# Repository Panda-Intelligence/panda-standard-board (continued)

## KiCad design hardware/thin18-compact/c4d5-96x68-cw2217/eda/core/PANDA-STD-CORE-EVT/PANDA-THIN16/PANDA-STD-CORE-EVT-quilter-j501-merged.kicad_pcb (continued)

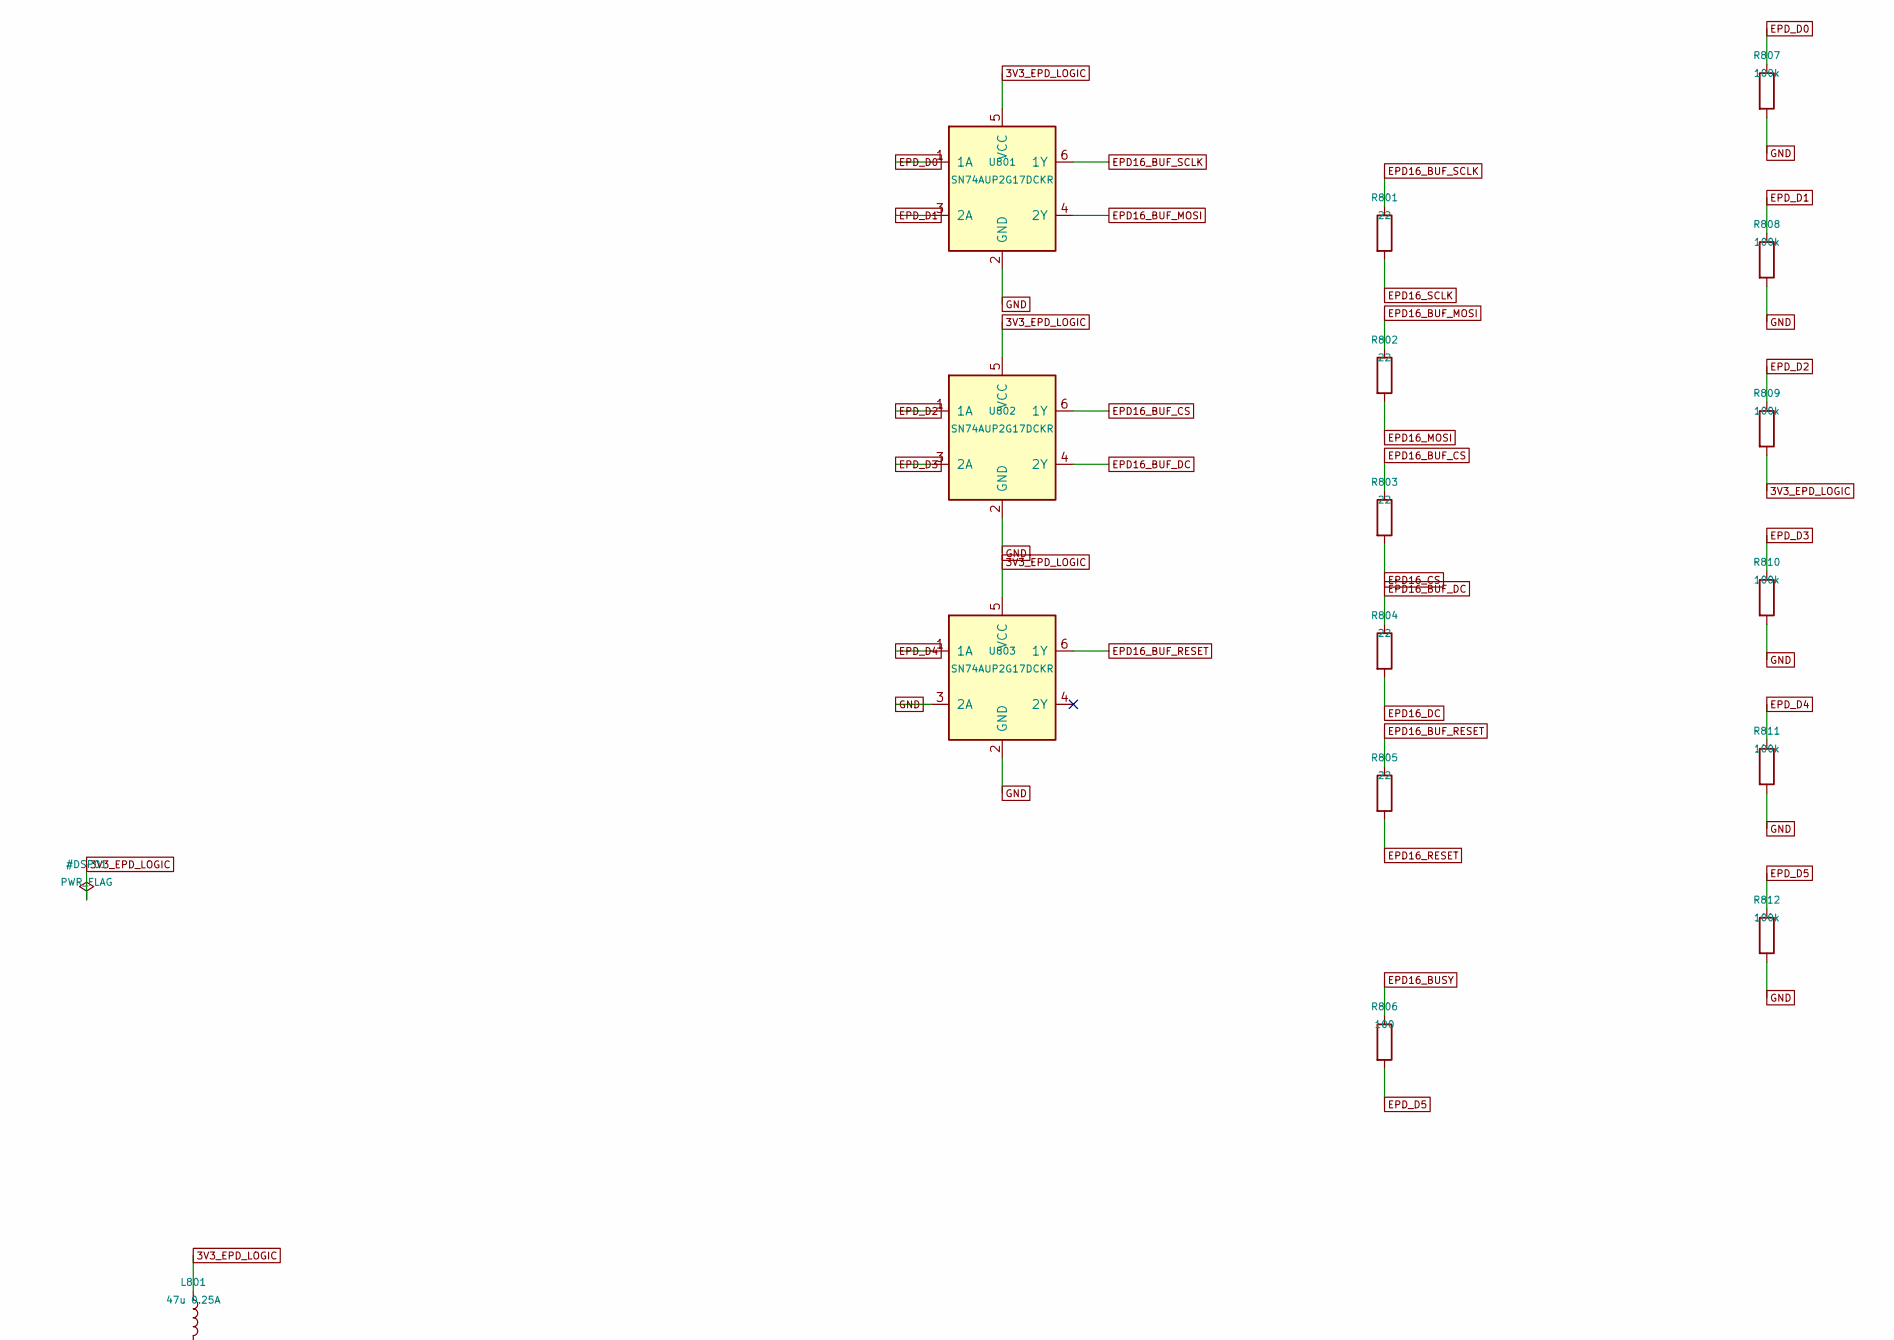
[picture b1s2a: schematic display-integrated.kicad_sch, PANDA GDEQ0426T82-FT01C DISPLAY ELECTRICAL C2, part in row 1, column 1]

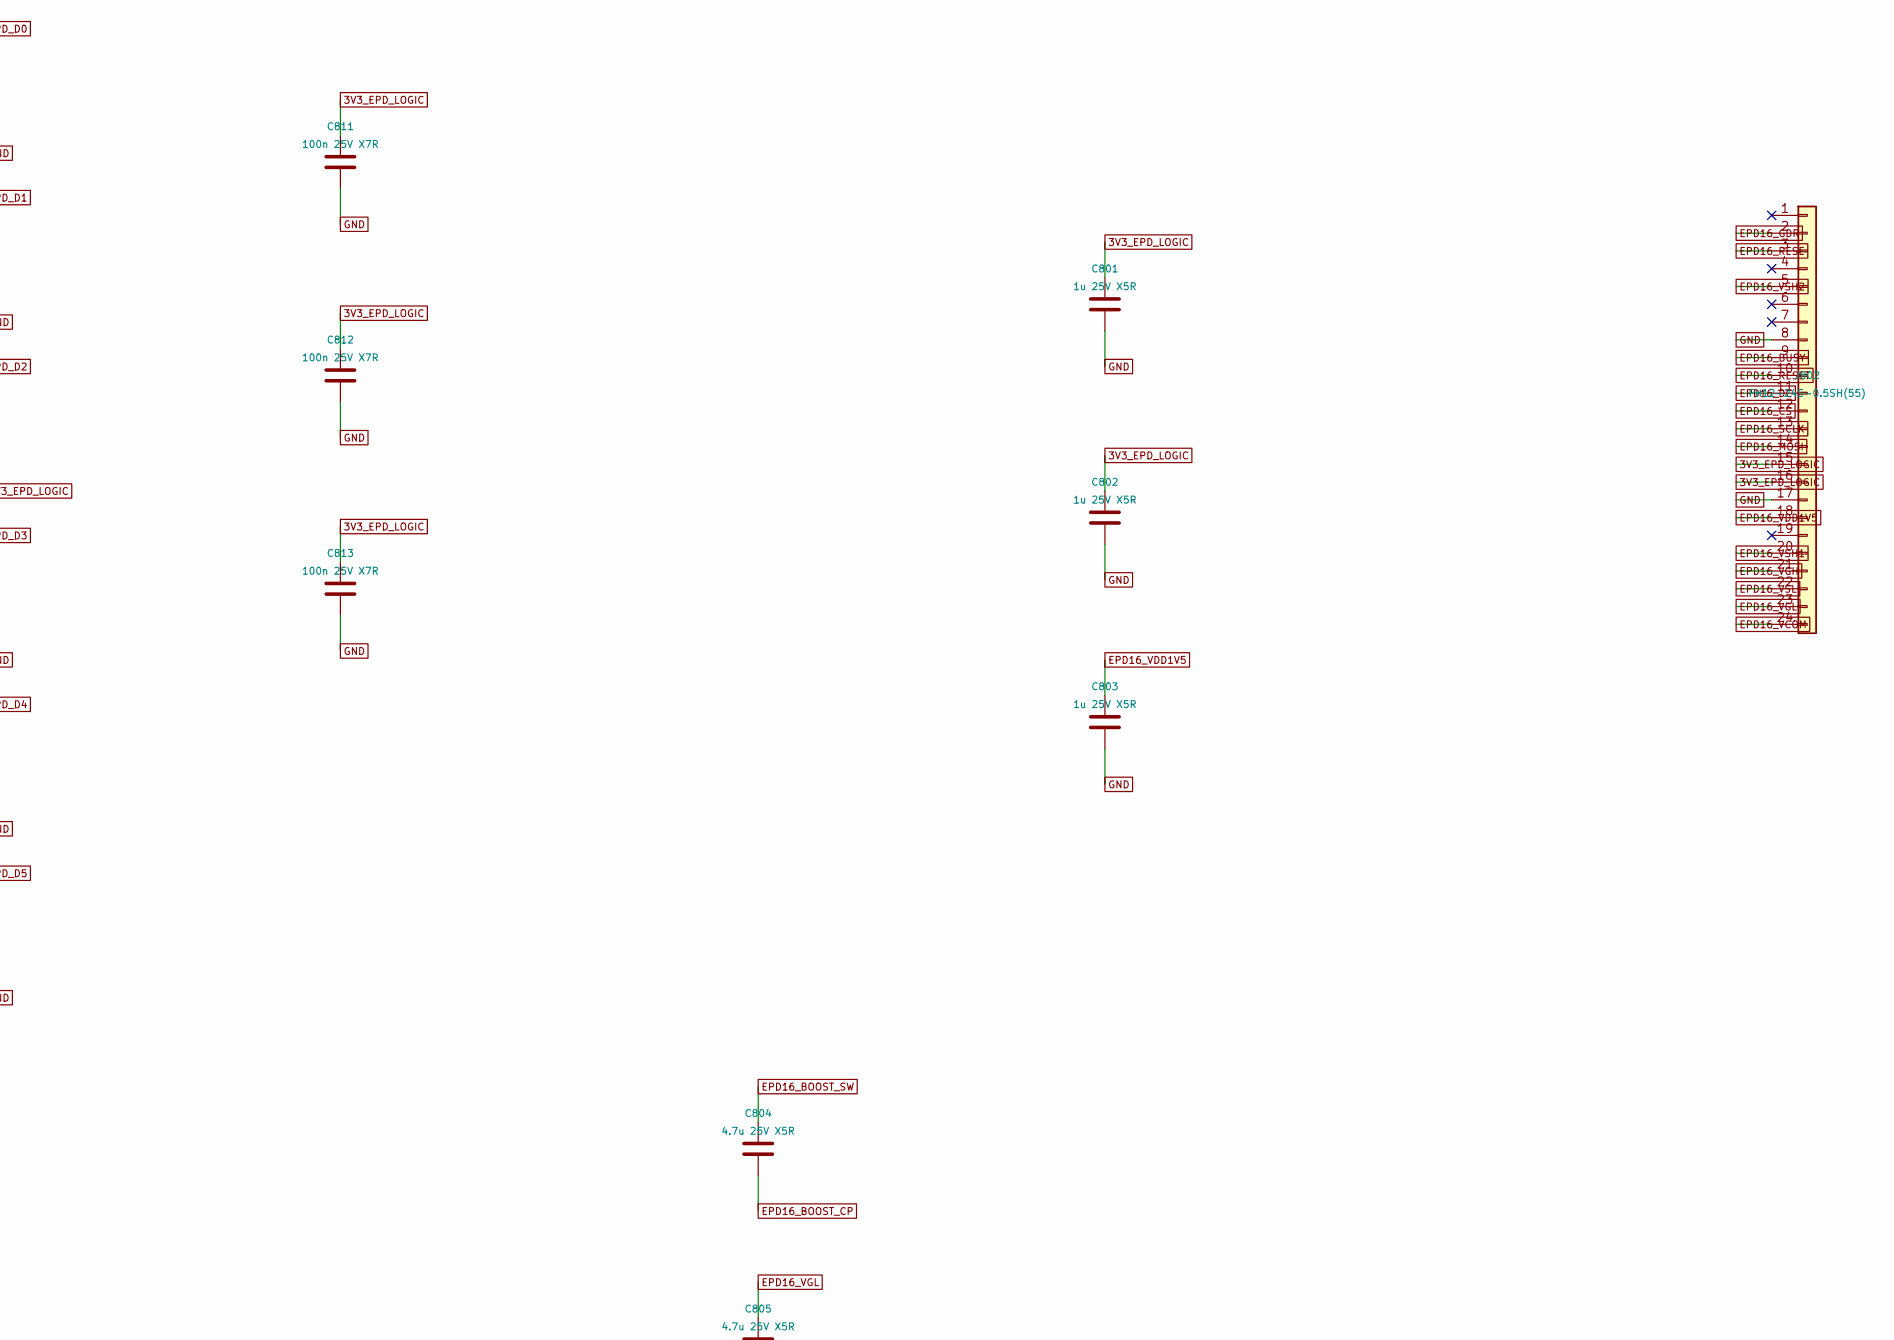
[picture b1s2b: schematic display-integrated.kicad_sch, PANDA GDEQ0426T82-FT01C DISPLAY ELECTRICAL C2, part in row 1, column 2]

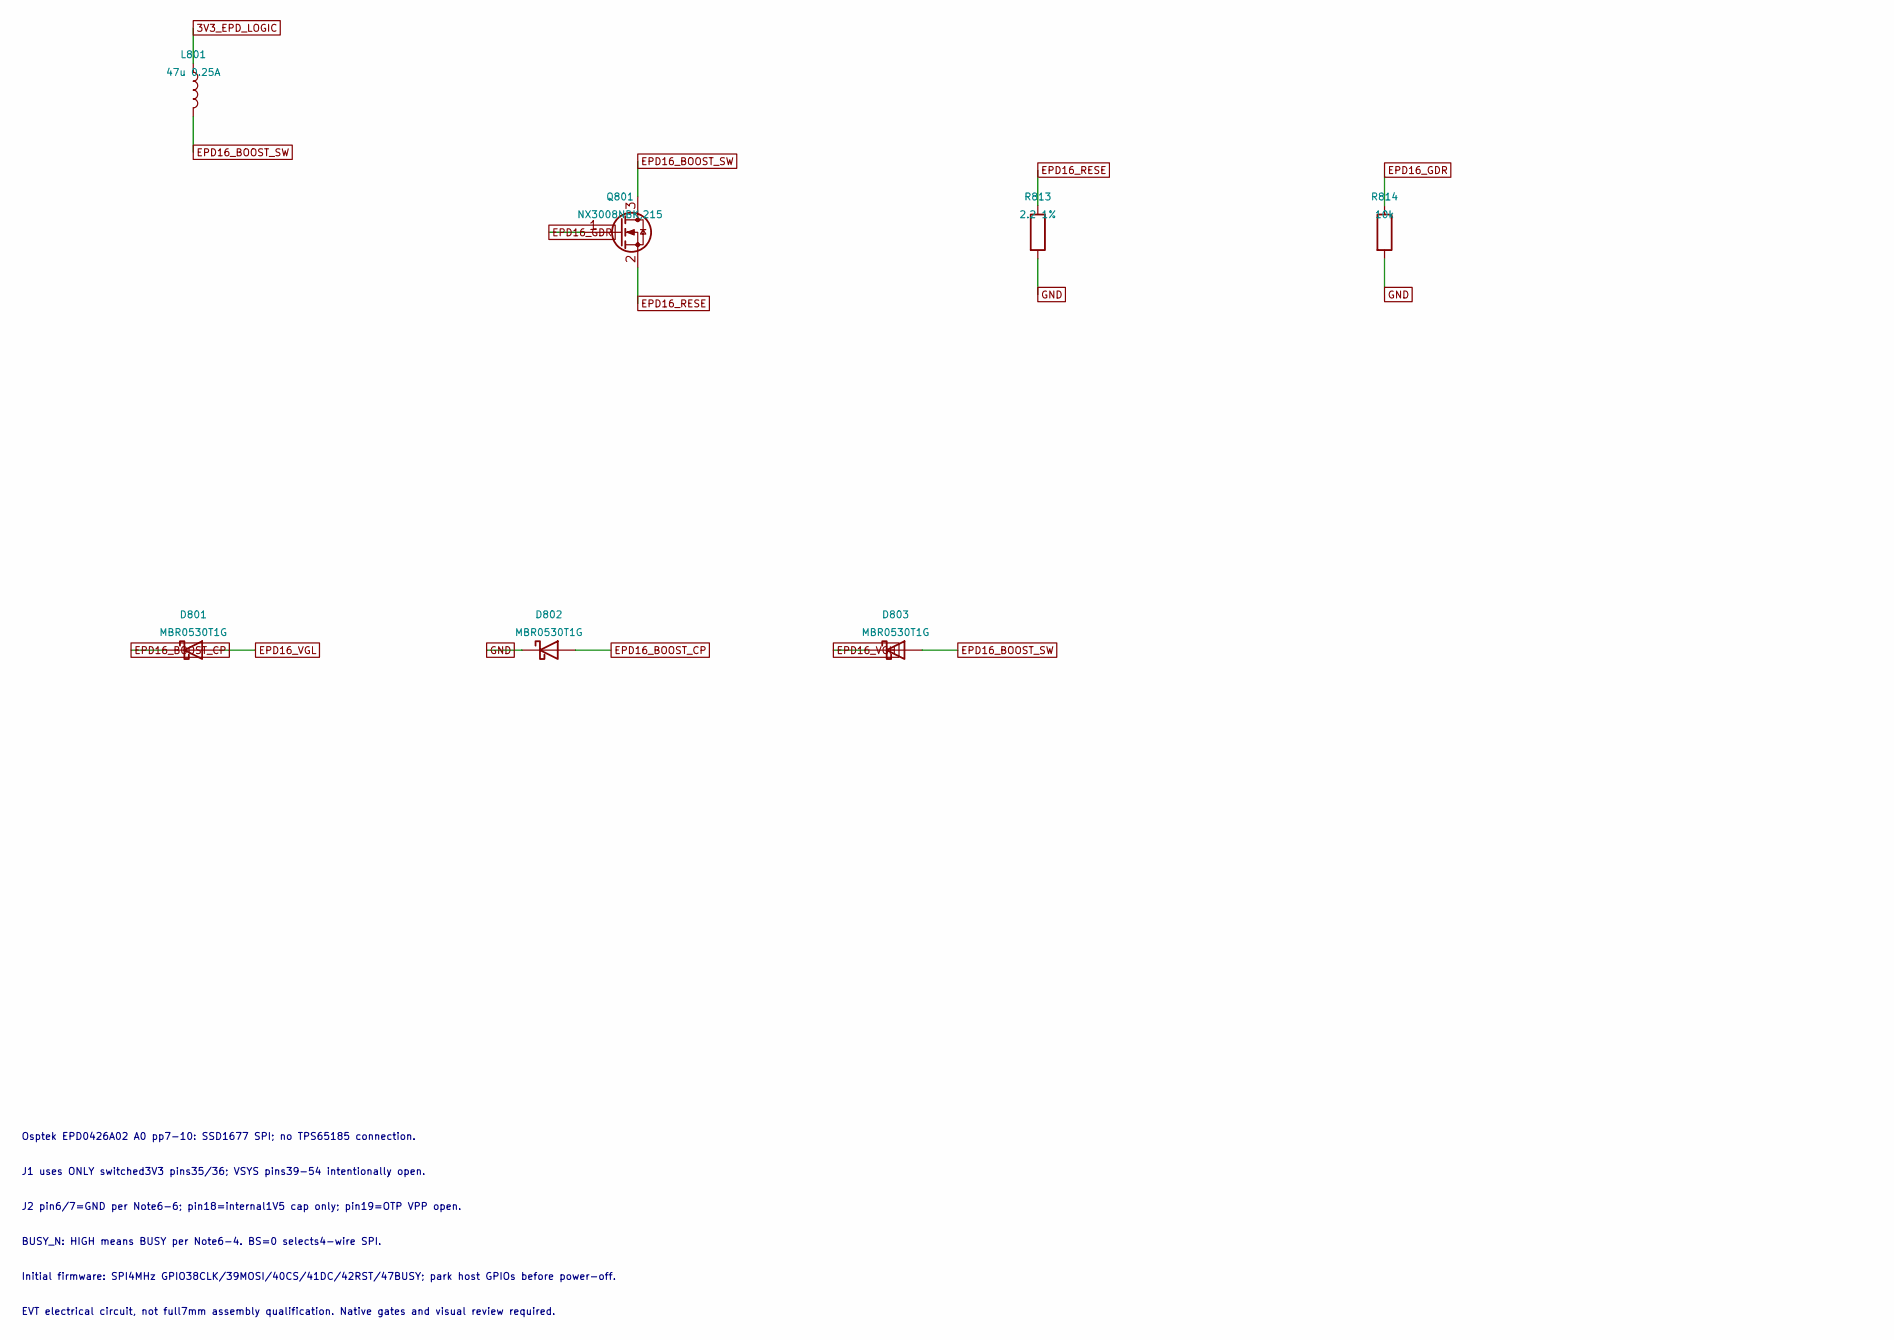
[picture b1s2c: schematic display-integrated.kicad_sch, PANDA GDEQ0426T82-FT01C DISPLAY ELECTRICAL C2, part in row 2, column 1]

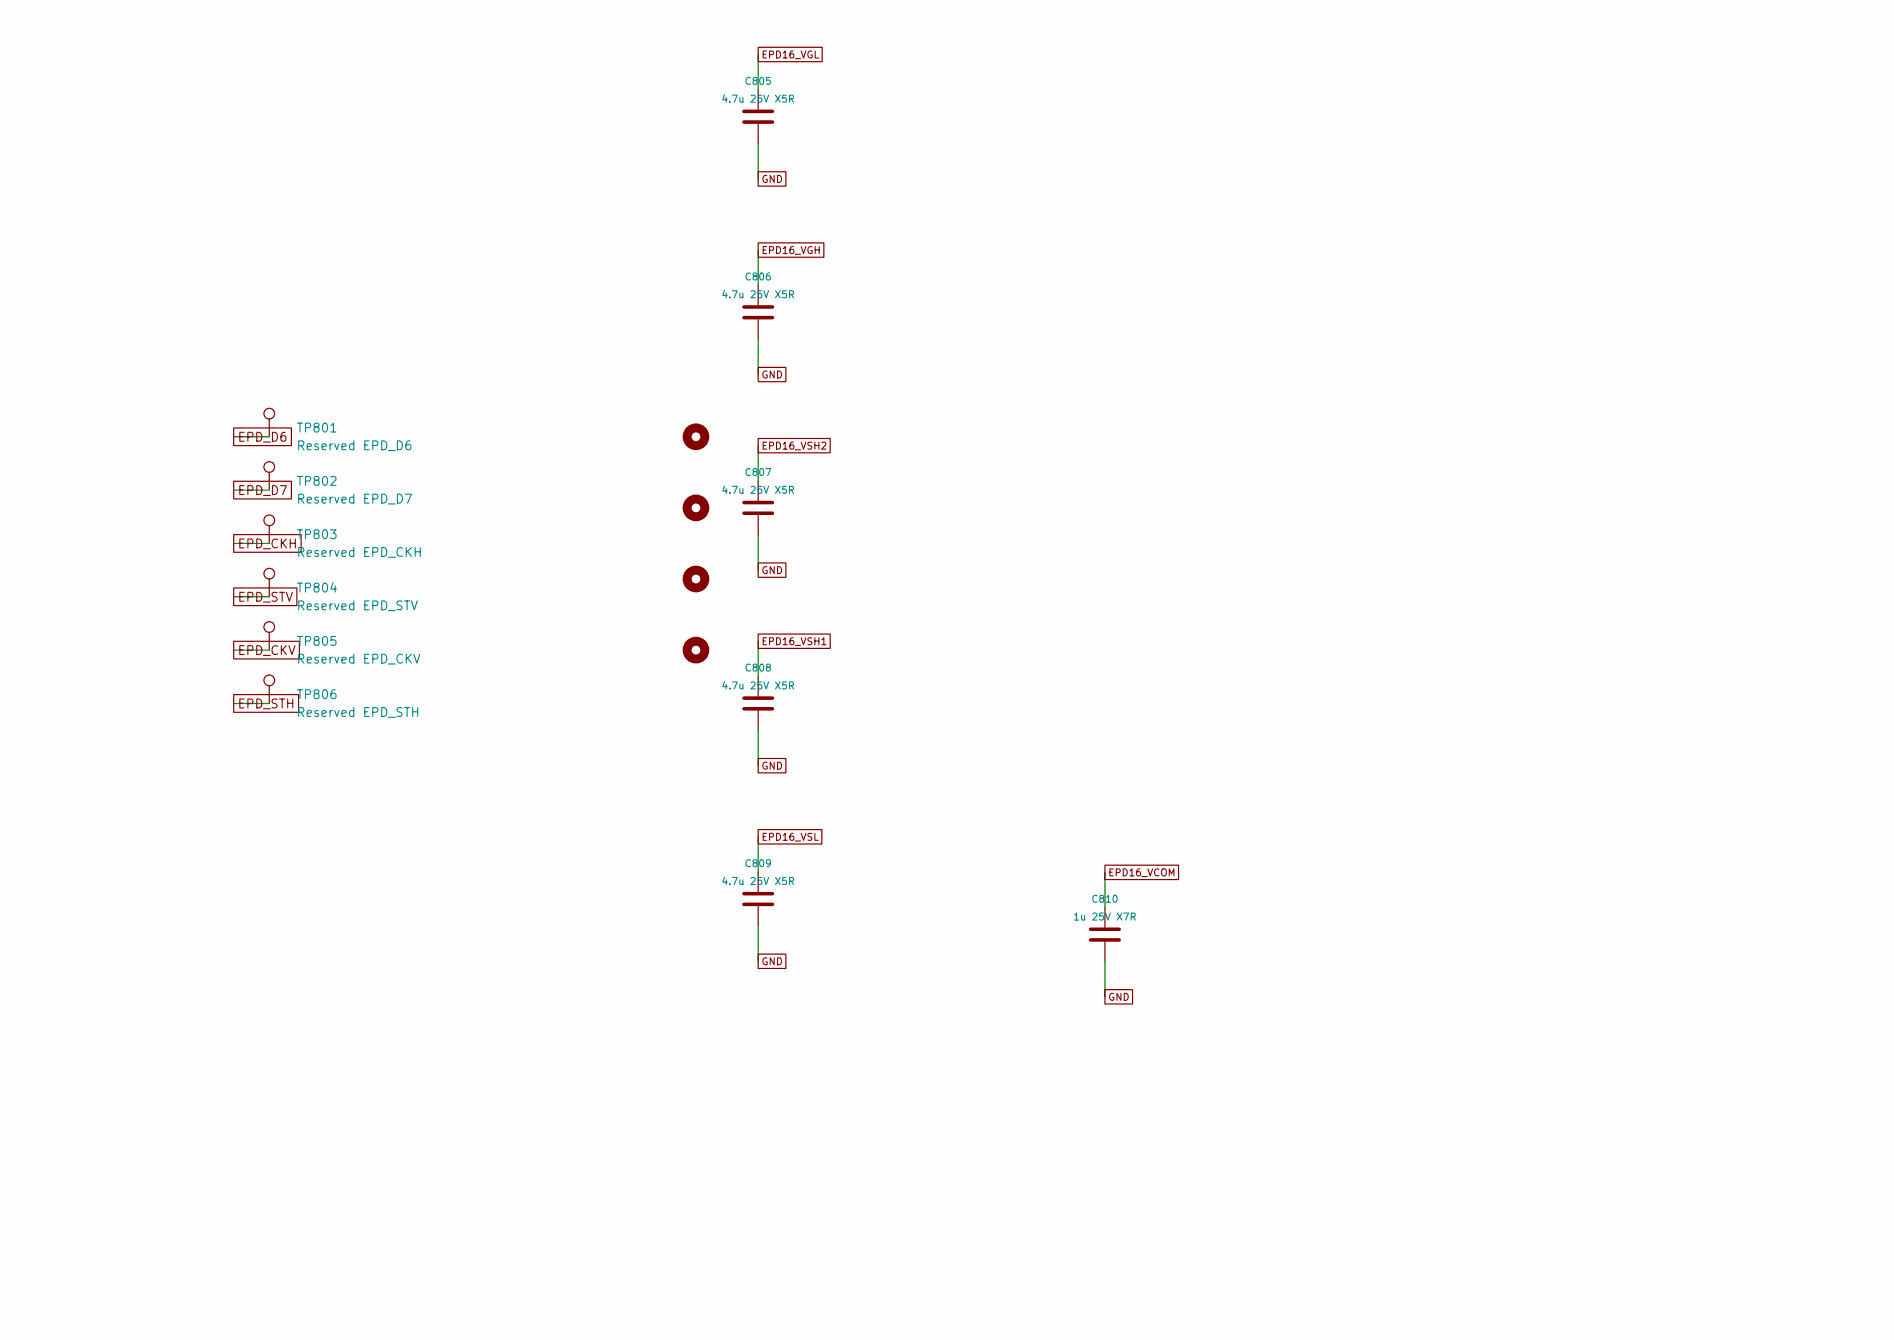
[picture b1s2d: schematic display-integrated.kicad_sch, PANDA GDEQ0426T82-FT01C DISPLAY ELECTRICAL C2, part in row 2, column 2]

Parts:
C801, C802, C803: 1u 25V X5R; C_0603_1608Metric; MPN 0603B105K250NT; LCSC C59302
C804, C805, C806, C807, C808, C809: 4.7u 25V X5R; C_0805_2012Metric; MPN GRM21BR61E475KA12L
C810: 1u 25V X7R; C_0805_2012Metric; MPN GRM21BR71E105KA99L
C811, C812, C813: 100n 25V X7R; C_0603_1608Metric; MPN GRM188R71E104KA01D
D801, D802, D803: MBR0530T1G; D_SOD-123; MPN MBR0530T1G
H801, H802, H803, H804: M1.2 clearance / NPTH 1.6; MountingHole_M1.2_1.6mm
J802: FH12-24S-0.5SH(55); Hirose_FH12-24S-0.5SH_1x24-1MP_P0.50mm_Horizontal; MPN FH12-24S-0.5SH(55)
L801: 47u 0.25A; L_Taiyo_NRH3010_3030; MPN LSXNE3030KKT470MN
Q801: NX3008NBK,215; SOT-23; MPN NX3008NBK,215
R801, R802, R803, R804, R805: 22; R_0402_1005Metric; MPN RC0402FR-0722RL
R806: 100; R_0402_1005Metric; MPN RC0402FR-07100RL
R807, R808, R809, R810, R811, R812: 100k; R_0402_1005Metric; Tolerance 1%; Voltage_Rating 50V; MPN 0402WGF1003TCE; LCSC C25741
R813: 2.2 1%; R_0603_1608Metric; MPN RC0603FR-072R2L
R814: 10k; R_0402_1005Metric; Tolerance 1%; Voltage_Rating 50V; MPN 0402WGF1002TCE; LCSC C25744
TP801: Reserved EPD_D6; TestPoint_Pad_D1.5mm
TP802: Reserved EPD_D7; TestPoint_Pad_D1.5mm
TP803: Reserved EPD_CKH; TestPoint_Pad_D1.5mm
TP804: Reserved EPD_STV; TestPoint_Pad_D1.5mm
TP805: Reserved EPD_CKV; TestPoint_Pad_D1.5mm
TP806: Reserved EPD_STH; TestPoint_Pad_D1.5mm
U801, U802, U803: SN74AUP2G17DCKR; SOT-363_SC-70-6; MPN SN74AUP2G17DCKR

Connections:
3V3_EPD_LOGIC: C801.1, C802.1, C811.1, C812.1, C813.1, J802.15, J802.16, L801.1, R809.2, U801.5 (VCC), U802.5 (VCC), U803.5 (VCC); also elsewhere on the board
EPD16_BOOST_CP: C804.2, D801.1 (K), D802.2 (A)
EPD16_BOOST_SW: C804.1, D803.2 (A), L801.2, Q801.3 (D)
EPD16_BUF_CS: R803.1, U802.6 (1Y)
EPD16_BUF_DC: R804.1, U802.4 (2Y)
EPD16_BUF_MOSI: R802.1, U801.4 (2Y)
EPD16_BUF_RESET: R805.1, U803.6 (1Y)
EPD16_BUF_SCLK: R801.1, U801.6 (1Y)
EPD16_BUSY: J802.9, R806.1
EPD16_CS: J802.12, R803.2
EPD16_DC: J802.11, R804.2
EPD16_GDR: J802.2, Q801.1 (G), R814.1
EPD16_MOSI: J802.14, R802.2
EPD16_RESE: J802.3, Q801.2 (S), R813.1
EPD16_RESET: J802.10, R805.2
EPD16_SCLK: J802.13, R801.2
EPD16_VCOM: C810.1, J802.24
EPD16_VDD1V5: C803.1, J802.18
EPD16_VGH: C806.1, D803.1 (K), J802.21
EPD16_VGL: C805.1, D801.2 (A), J802.23
EPD16_VSH1: C808.1, J802.20
EPD16_VSH2: C807.1, J802.5
EPD16_VSL: C809.1, J802.22
EPD_CKH: TP803.1; also elsewhere on the board
EPD_CKV: TP805.1; also elsewhere on the board
EPD_D0: R807.1, U801.1 (1A); also elsewhere on the board
EPD_D1: R808.1, U801.3 (2A); also elsewhere on the board
EPD_D2: R809.1, U802.1 (1A); also elsewhere on the board
EPD_D3: R810.1, U802.3 (2A); also elsewhere on the board
EPD_D4: R811.1, U803.1 (1A); also elsewhere on the board
EPD_D5: R806.2, R812.1; also elsewhere on the board
EPD_D6: TP801.1; also elsewhere on the board
EPD_D7: TP802.1; also elsewhere on the board
EPD_STH: TP806.1; also elsewhere on the board
EPD_STV: TP804.1; also elsewhere on the board
GND: C801.2, C802.2, C803.2, C805.2, C806.2, C807.2, C808.2, C809.2, C810.2, C811.2, C812.2, C813.2, D802.1 (K), J802.8, J802.17, R807.2, R808.2, R810.2, R811.2, R812.2, R813.2, R814.2, U801.2 (GND), U802.2 (GND), U803.2 (GND), U803.3 (2A); also elsewhere on the board

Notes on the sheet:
Osptek EPD0426A02 A0 pp7-10: SSD1677 SPI; no TPS65185 connection.
J1 uses ONLY switched3V3 pins35/36; VSYS pins39-54 intentionally open.
J2 pin6/7=GND per Note6-6; pin18=internal1V5 cap only; pin19=OTP VPP open.
BUSY_N: HIGH means BUSY per Note6-4. BS=0 selects4-wire SPI.
Initial firmware: SPI4MHz GPIO38CLK/39MOSI/40CS/41DC/42RST/47BUSY; park host GPIOs before power-off.
EVT electrical circuit, not full7mm assembly qualification. Native gates and visual review required.

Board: 4 copper layers, 180 parts (27 on the bottom side), 112 nets, no tracks yet.

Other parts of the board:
C209: 1u; C_0603_1608Metric
C301: CPH3225A 11mF 3.3V RTC backup candidate; C_1210_3225Metric
C514, C515: DNP / USB tuning; C_0402_1005Metric
D201: TPD4E05U06DQAR; USON-10_2.5x1.0mm_P0.5mm
D202: TPD1E10B06DPYR; Texas_DPY0002A_0.6x1mm_P0.65mm
J201: USB4500-03-0-A; USB4500_08mm_MidMount_LayoutReview
J302: SM03B-SRSS-TB NTC; JST_SH_SM03B-SRSS-TB_1x03-1MP_P1.00mm_Horizontal
R206, R207: 5.1k / USB-C Rd; R_0402_1005Metric
R529, R530: 22; R_0402_1005Metric
R615: 5.23k; R_0603_1608Metric
R616: 30.1k; R_0603_1608Metric

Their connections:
BQ_TS: J302.1, R615.2, R616.1; also elsewhere on the board
GND: C209.2, C301.2, C514.2, C515.2, D201.3, D201.8, D202.2, J201.A1, J201.A12, J201.B1, J201.B12, J201.SH, J302.2, R206.1, R207.1, R616.2; also elsewhere on the board
RTC_VBACKUP: C301.1; also elsewhere on the board
SGM41513_REGN: R615.1; also elsewhere on the board
USB_CC1: D201.4, J201.A5, R206.2
USB_CC2: D201.5, J201.B5, R207.2
USB_DM: D201.2, J201.A7, J201.B7, R530.1
USB_DM_MCU: C515.1, R530.2; also elsewhere on the board
USB_DP: D201.1, J201.A6, J201.B6, R529.1
USB_DP_MCU: C514.1, R529.2; also elsewhere on the board
VBUS_USB: C209.1, D202.1, J201.A4, J201.A9, J201.B4, J201.B9; also elsewhere on the board
